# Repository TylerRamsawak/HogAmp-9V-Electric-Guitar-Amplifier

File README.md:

# HogAmp: 9V Electric Guitar Amplifier
I made a very simple, portable guitar amplifier. Its based off the LM386N-1 and is designed to run off a single 9V battery. I travel a lot to-and-fro school and bringing my 10W amp, while small, is becoming annoying. Its a bit too big to fit in a backpack and needs mains ac to run. With my amp, these problems are gone in exchange for power and quality. However, for practice, this is not a concern to me. The HogAmp's name is inspired by the Pignose brand of amps. Those are too expensive for me, so here is my compromise!
<br>
### 3D Render of Enclosure

<br>
<div class="table_component" role="region" tabindex="0">
<table>
    <caption>BOM</caption>
    <thead>
        <tr>
            <th>Reference</th>
            <th>Quantity</th>
            <th>Value</th>
            <th>LCSC ID</th>
            <th>Price</th>
            <th>Ext. Price</th>
        </tr>
    </thead>
    <tbody>
        <tr>
            <td>U1</td>
            <td>1</td>
            <td>LM386N-1</td>
            <td>N/A</td>
            <td>$0.85</td>
            <td>$1.70</td>
        </tr>
        <tr>
            <td>C1,C3</td>
            <td>2</td>
            <td>10uF</td>
            <td>N/A</td>
            <td>$0.09</td>
            <td>$0.18</td>
        </tr>
        <tr>
            <td>C2</td>
            <td>1</td>
            <td>1000uF</td>
            <td>N/A</td>
            <td>$0.30</td>
            <td>$0.30</td>
        </tr>
        <tr>
            <td>C4</td>
            <td>1</td>
            <td>330nF</td>
            <td>N/A</td>
            <td>$0.18</td>
            <td>$0.18</td>
        </tr>
      <tr>
            <td>J1,J3</td>
            <td>2</td>
            <td>Toggle Switch</td>
            <td>N/A</td>
            <td>$0.47</td>
            <td>$0.94</td>
        </tr>
      <tr>
            <td>J4,J5,J7</td>
            <td>3</td>
            <td>10k Log. Potentiometers</td>
            <td>N/A</td>
            <td>$0.50</td>
            <td>$1.50</td>
        </tr>
      <tr>
            <td>J4,J5,J7</td>
            <td>3</td>
            <td>Potentiometer Dust Seals</td>
            <td>N/A</td>
            <td>$0.04</td>
            <td>$0.12</td>
        </tr>
      <tr>
            <td>J2</td>
            <td>1</td>
            <td>1/4" Female Jack</td>
            <td>N/A</td>
            <td>$0.87</td>
            <td>$1.74</td>
        </tr>
      <tr>
            <td>BT1</td>
            <td>1</td>
            <td>9V Clip</td>
            <td>N/A</td>
            <td>$0.10</td>
            <td>$0.10</td>
        </tr>
        <tr>
            <td>Total: $6.67 + $16.44(cheapest shipping & tariff)</td>
        </tr>
      <tr>
            <td>Grand Total: $23.20</td>
        </tr>
    </tbody>
</table>
</div>
I bought some extras incase I blew something up. Also, since when was shipping so expensive?! This is the cheapest option. In the future, I will buy bulk components all at once.
<h3>3D Model</h3>

<h3>PCB</h3>

<h3>Schematic</h3>

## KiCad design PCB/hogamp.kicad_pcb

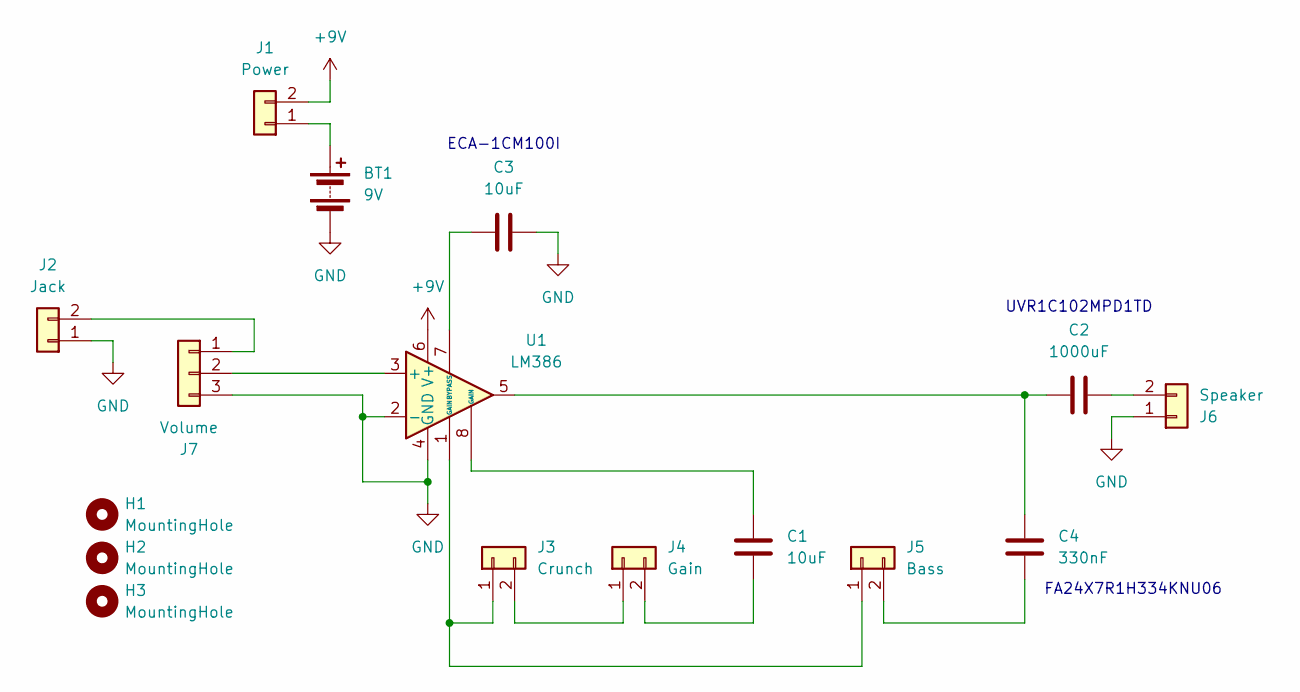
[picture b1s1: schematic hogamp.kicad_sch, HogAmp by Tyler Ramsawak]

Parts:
BT1: 9V; Samtec_HPM-02-05-x-S_Straight_1x02_Pitch5.08mm
C1, C3: 10uF; CP_Radial_D5.0mm_P2.50mm
C2: 1000uF; CP_Radial_D10.0mm_P5.00mm
C4: 330nF; CAPRB500W50L450T300H550
H1, H2, H3: MountingHole; MountingHole_3.2mm_M3
J1: Power; Samtec_HPM-02-05-x-S_Straight_1x02_Pitch5.08mm
J2: Jack; Samtec_HPM-02-05-x-S_Straight_1x02_Pitch5.08mm
J3: Crunch; Samtec_HPM-02-05-x-S_Straight_1x02_Pitch5.08mm
J4: Gain; Samtec_HPM-02-05-x-S_Straight_1x02_Pitch5.08mm
J5: Bass; Samtec_HPM-02-05-x-S_Straight_1x02_Pitch5.08mm
J6: Speaker; Samtec_HPM-02-05-x-S_Straight_1x02_Pitch5.08mm
J7: Volume; Samtec_HPM-03-01-x-S_Straight_1x03_Pitch5.08mm
U1: LM386; DIP-8_W7.62mm_Socket

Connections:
+9V: J1.2, U1.6 (V+)
GND: BT1.2 (-), C3.2, J2.1, J6.1, J7.3, U1.2 (-), U1.4 (GND)
unnamed: BT1.1 (+), J1.1
unnamed: C1.1, U1.8 (GAIN)
unnamed: C2.1, C4.1, U1.5
unnamed: J2.2, J7.1
unnamed: J3.1, J5.1, U1.1 (GAIN)
unnamed: J3.2, J4.1
unnamed: C1.2, J4.2
unnamed: C4.2, J5.2
unnamed: C2.2, J6.2
unnamed: J7.2, U1.3 (+)
unnamed: C3.1, U1.7 (BYPASS)

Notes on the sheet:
ECA-1CM100I
FA24X7R1H334KNU06
UVR1C102MPD1TD

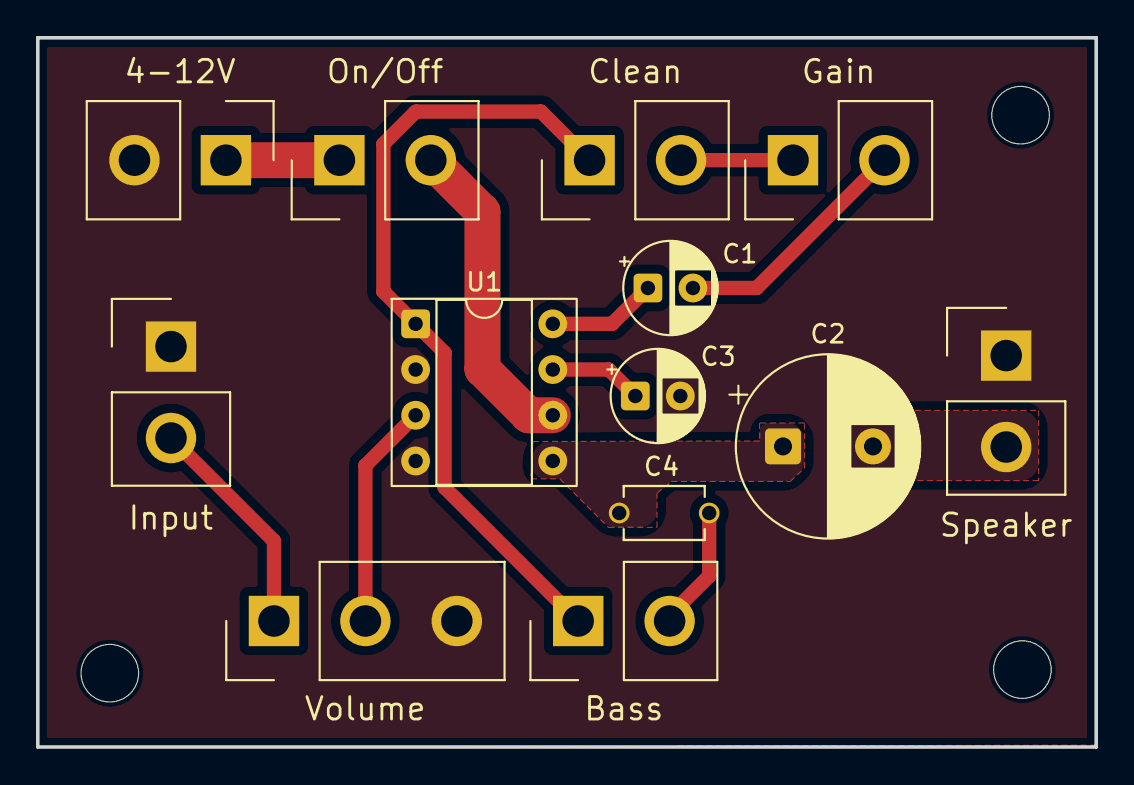
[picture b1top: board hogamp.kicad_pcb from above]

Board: 2 copper layers, 58.8 x 39.4 mm, 16 parts (0 on the bottom side), 13 nets.

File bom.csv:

Designator,Footprint,Quantity,Value,LCSC Part #
BT1,Samtec_HPM-02-05-x-S_Straight_1x02_Pitch5.08mm,1,9V,
"C1, C3",CP_Radial_D5.0mm_P2.50mm,2,10uF,
C2,CP_Radial_D10.0mm_P5.00mm,1,1000uF,
C4,CAPRB500W50L450T300H550,1,330nF,
J1,Samtec_HPM-02-05-x-S_Straight_1x02_Pitch5.08mm,1,Power,
J2,Samtec_HPM-02-05-x-S_Straight_1x02_Pitch5.08mm,1,Jack,
J3,Samtec_HPM-02-05-x-S_Straight_1x02_Pitch5.08mm,1,Crunch,
J4,Samtec_HPM-02-05-x-S_Straight_1x02_Pitch5.08mm,1,Gain,
J5,Samtec_HPM-02-05-x-S_Straight_1x02_Pitch5.08mm,1,Bass,
J6,Samtec_HPM-02-05-x-S_Straight_1x02_Pitch5.08mm,1,Speaker,
J7,Samtec_HPM-03-01-x-S_Straight_1x03_Pitch5.08mm,1,Volume,
U1,DIP-8_W7.62mm_Socket,1,LM386,

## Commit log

2025-11-30 Revise README with detailed project description
    Expanded the README to provide a detailed description of the HogAmp, including its purpose, components, and pricing. Added sections for 3D model, PCB, and schematic images.
2025-11-30 Add journal entry for PCB design and circuit details
    Documented the PCB layout, component selection, and designed circuit for an audio amplifier using the LM386. Included images of the layout, schematic, and component footprints.
2025-12-02 Include 3D renders in README
    Added 3D renders of the amplifier enclosure to the README.
